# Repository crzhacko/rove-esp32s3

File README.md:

# ROVE — ESP32-S3 RC/Voice Car Platform

Offline voice-controlled toy car platform based on the **ESP32-S3-WROOM-1**.
No internet required — all speech recognition runs on-device via
[ESP-SR](https://github.com/espressif/esp-sr).

## Variants

| Variant  | Motors | Servos | Voice | PCB            |
|----------|:------:|:------:|:-----:|----------------|
| ROVE     | ✓      |        |       | placeholder    |
| ROVE-S   | ✓      | ✓      |       | placeholder    |
| ROVE-V   | ✓      |        | ✓     | **routed** ✓   |
| ROVE-SV  | ✓      | ✓      | ✓     | placeholder    |
| ROVE-SVX | ✓      | ✓      | ✓+    | placeholder    |

See [`docs/rove_variants.md`](docs/rove_variants.md) for full pin assignment,
build instructions, and BOM.

## Repository layout

```
rove_esp32s3/
├── electronics/
│   ├── libs/               shared KiCad symbols (TODO: rove.kicad_sym)
│   ├── rove/               ROVE placeholder schematic
│   ├── rove_s/             ROVE-S placeholder schematic
│   ├── rove_v/             ROVE-V full KiCad schematic + routed PCB ← start here
│   ├── rove_sv/            ROVE-SV placeholder schematic
│   └── rove_svx/           ROVE-SVX placeholder schematic
├── firmware/
│   ├── CMakeLists.txt      top-level ESP-IDF project
│   ├── main/               app_main, Kconfig variant selector
│   ├── components/
│   │   ├── motor/          DRV8833 DC motor driver
│   │   ├── servo/          LEDC PWM servo driver
│   │   └── voice/          INMP441 I2S + ESP-SR recognition pipeline
│   └── configs/            per-variant sdkconfig fragments
├── tools/                  Python scripts for KiCad generation
└── docs/
    ├── rove_variants.md    variant comparison + build guide
    └── bom/                per-variant bill of materials
```

## Quick start (ROVE-V)

```bash
# 1. Install ESP-IDF v5.x
# 2. Clone and enter firmware directory
cd firmware

# 3. Apply ROVE-V sdkconfig
cp configs/sdkconfig.rove_v sdkconfig.defaults

# 4. Build and flash
idf.py set-target esp32s3
idf.py build
idf.py -p /dev/ttyUSB0 flash monitor
```

Wake word: **"Hey ESP"** — then say "go forward", "turn left", "stop", etc.

## Hardware (ROVE-V)

- **MCU**: ESP32-S3-WROOM-1 (16 MB flash, 8 MB PSRAM)
- **Motor driver**: DRV8833PW dual H-bridge
- **Charger**: TP4056 via USB-C (580 mA)
- **LDO**: XC6220B331MR (3.3 V)
- **Microphone**: INMP441 I2S MEMS
- **Board**: 60 × 50 mm (smaller than Arduino Uno)

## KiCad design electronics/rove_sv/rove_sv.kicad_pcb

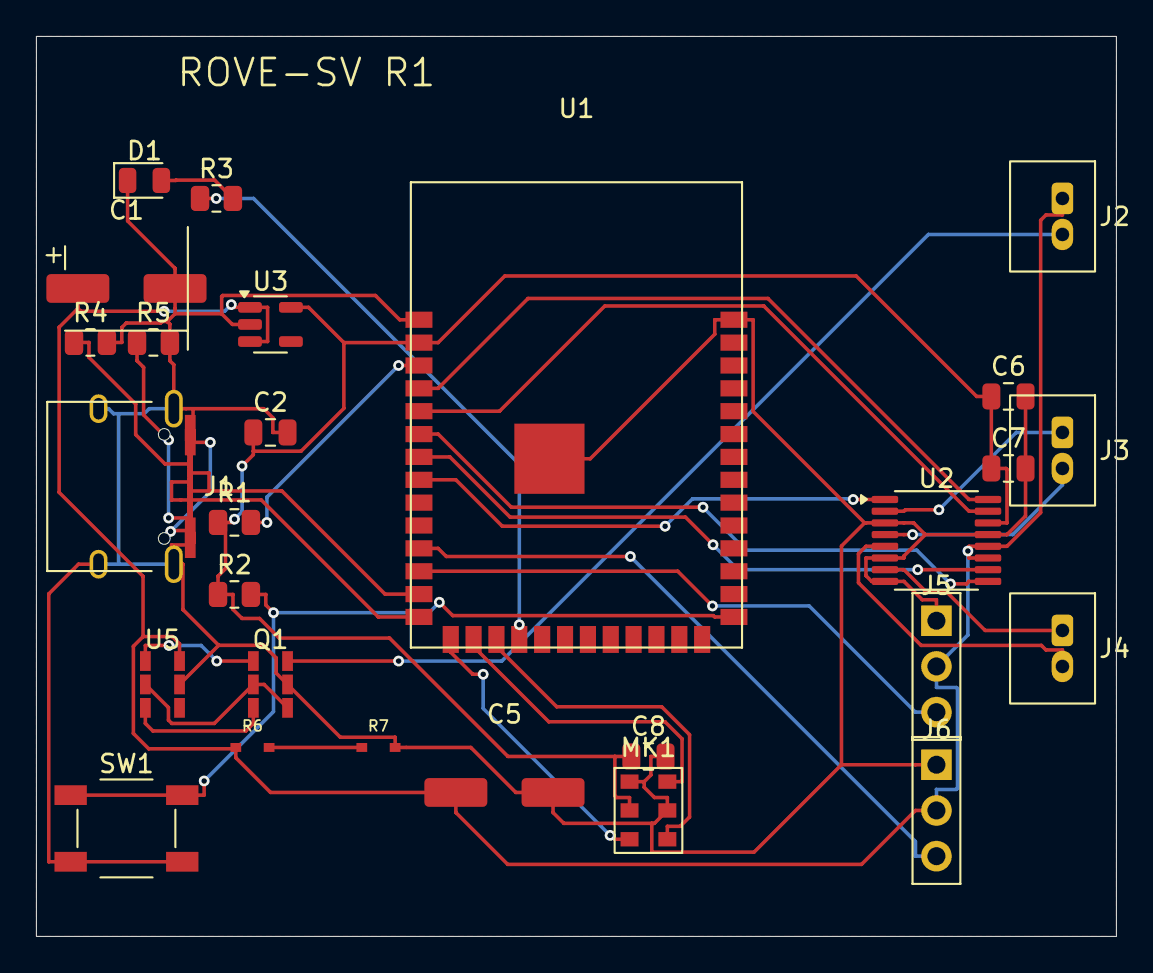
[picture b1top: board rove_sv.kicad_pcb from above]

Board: 2 copper layers, 60.0 x 50.0 mm, 27 parts (0 on the bottom side), 31 nets.

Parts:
C1: 10uF; CP_Elec_6.3x5.8
C2, C7: 0.1uF; C_0805_2012Metric
C5: 100uF; CP_Elec_6.3x5.8
C6: 10nF; C_0805_2012Metric
C8: 100nF; C_0805_2012Metric
D1: Blue; LED_0805_2012Metric
J1: USB-C; USB_C_Receptacle_HRO_TYPE-C-31-M-12
J2: Battery; JST_PH_B2B-PH-K_1x02_P2.00mm_Vertical
J3: LeftMotor; JST_PH_B2B-PH-K_1x02_P2.00mm_Vertical
J4: RightMotor; JST_PH_B2B-PH-K_1x02_P2.00mm_Vertical
J5: Servo1; PinHeader_1x03_P2.54mm_Vertical
J6: Servo2; PinHeader_1x03_P2.54mm_Vertical
MK1: INMP441; INMP441_LGA-6
Q1: FS8205A; SOT-23-6
R1, R2: 10k; R_0805_2012Metric
R3: 330R; R_0805_2012Metric
R4, R5: 5.1k; R_0805_2012Metric
R6: 100k; R_0402_1005Metric
R7: 47k; R_0402_1005Metric
SW1: BOOT; SW_SPST_SKQG_WithoutStem
U1: ESP32-S3-WROOM-1
U2: DRV8833PW; TSSOP-16_4.4x5mm_P0.65mm
U3: XC6220B331MR; SOT-23-5
U5: DW01A; SOT-23-6

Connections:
/3V3: C2.1, C6.1, C7.1, C8.1, MK1.4, R1.1, R2.1, U1.2, U2.14, U3.5
/AOUT1: J3.1, U2.2
/AOUT2: J3.2, U2.4
/BATT_NEG: J2.2, Q1.4
/BOUT1: J4.1, U2.7
/BOUT2: J4.2, U2.5
/CC1: J1.A5, R4.1
/CC2: J1.B5, R5.1
/DRV_SLEEP: U1.8, U2.1
/DW01_OC: Q1.3, U5.3
/DW01_OD: Q1.1, U5.1
/EN: R1.2, U1.3
/I2S_SCK: MK1.6, U1.16
/I2S_SD: MK1.2, U1.17
/I2S_WS: MK1.5, U1.15
/IO0: R2.2, SW1.1, U1.27
/LED_ANODE: D1.A, R3.2
/LEFT_IN1: U1.4, U2.16
/LEFT_IN2: U1.5, U2.15
/PROT_CS: Q1.2, Q1.6, U5.2
/RIGHT_IN1: U1.6, U2.9
/RIGHT_IN2: U1.7, U2.10
/SERVO1: J5.3, U1.12
/SERVO2: J6.3, U1.11
/STATUS_LED: R3.1, U1.18
/USB_5V: J1.A4, J1.A9, J1.B4, J1.B9
/USB_D+: J1.A6, J1.B6, U1.14
/USB_D-: J1.A7, J1.B7, U1.13
/VBAT: C1.1, C5.1, J2.1, J5.2, J6.2, R6.1, U2.11, U2.12, U3.1, U3.3, U5.4
/VBAT_MON: R6.2, R7.1
GND: C1.2, C2.2, C5.2, C6.2, C7.2, C8.2, D1.K, J1.A1, J1.A12, J1.B1, J1.B12, J1.S1, J5.1, J6.1, MK1.1, MK1.3, Q1.5, R4.2, R5.2, R7.2, SW1.2, U1.1, U1.40, U1.41, U2.3, U2.6, U2.8, U2.13, U3.2, U5.5

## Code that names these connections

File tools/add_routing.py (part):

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# ── net numbers (from (net N "name") declarations) ────────────────────────────
GND        = 1
V3V3       = 2
USB_5V     = 3
VBAT       = 4
LEFT_IN1   = 11
LEFT_IN2   = 12
RIGHT_IN1  = 13
RIGHT_IN2  = 14
DRV_SLEEP  = 15
AOUT1      = 16
AOUT2      = 17
BOUT1      = 18
BOUT2      = 19
I2S_WS     = 22
I2S_SCK    = 23
I2S_SD     = 24

# ── absolute pad positions (component_pos + relative_pad_pos) ─────────────────
# U1 ESP32-S3-WROOM-1 @ (30, 25) — left-side pads (x=-8.75 rel)
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
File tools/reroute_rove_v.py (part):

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T(21.25, 28.63, 21.5, 28.63, F_CU, "/DRV_SLEEP", W)
V(21.5, 28.63, "/DRV_SLEEP")
T(21.5, 28.63, 21.5, 50.0, B_CU, "/DRV_SLEEP", W)    # south (clear of I2S/IO0 which go to y≤48.6)
T(21.5, 50.0, 55.0, 50.0, B_CU, "/DRV_SLEEP", W)     # east to x=55
T(55.0, 50.0, 55.0, 31.5, B_CU, "/DRV_SLEEP", W)     # north (x=55 west of all motor south columns)
V(55.0, 31.5, "/DRV_SLEEP")
T(55.0, 31.5, 65.138, 31.5, F_CU, "/DRV_SLEEP", W)   # east at y=31.5 (above 3V3 bus at y=34.05)
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#   VBAT B.Cu col (y=18→42), I2S/IO0 verticals (x=23-39, all west of south columns x≥57)
# Column x: AOUT1=73, AOUT2=74.5, BOUT2=77.5, BOUT1=79 (VBAT B.Cu at x=76 between BOUT2/BOUT1)
# F.Cu approaches: AOUT1 y=21, AOUT2 y=19 (different y to avoid crossing)
# BOUT2 exits west to x=58.5 so its B.Cu south col doesn't cross AOUT1 east at y=44
# =============================================================================
# AOUT1: U2.pad2 (65.138,33.375) → J3.pad1 (70,20)
# Via at x=64 (stub stays x>62.05 so no overlap with 3V3 F.Cu bus).
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# F.Cu approach at y=23 separates from AOUT2 at y=19 (4mm gap).
T(65.138, 33.375, 64.0, 33.375, F_CU, "/AOUT1", W)    # short W stub (x≥62.05 ✓)
V(64.0, 33.375, "/AOUT1", drill=0.4, size=0.8)
T(64.0, 33.375, 64.0, 44.0, B_CU, "/AOUT1", WM)      # south to y=44
T(64.0, 44.0, 73.5, 44.0, B_CU, "/AOUT1", WM)        # east at y=44 to x=73.5
T(73.5, 44.0, 73.5, 23.0, B_CU, "/AOUT1", WM)        # north col x=73.5 (J4.pad2 copper edge=72.6; gap=73.0-72.6=0.4mm ✓)
V(73.5, 23.0, "/AOUT1", drill=0.4, size=0.8)
T(73.5, 23.0, 70.0, 23.0, F_CU, "/AOUT1", WM)        # west at y=23
T(70.0, 23.0, 70.0, 20.0, F_CU, "/AOUT1", WM)        # south → J3.pad1

# AOUT2: U2.pad4 (65.138,34.675) → J3.pad2 (72,20)
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T(58.5, 46.5, 77.5, 46.5, B_CU, "/BOUT2", WM)       # east at y=46.5
T(77.5, 46.5, 77.5, 27.0, B_CU, "/BOUT2", WM)       # north to y=27 (x=77.5 east of VBAT x=76)
V(77.5, 27.0, "/BOUT2", drill=0.4, size=0.8)
T(77.5, 27.0, 72.0, 27.0, F_CU, "/BOUT2", WM)       # west at y=27
T(72.0, 27.0, 72.0, 28.0, F_CU, "/BOUT2", WM)       # → J4.pad2

# BOUT1: U2.pad7 (65.138,36.625) → J4.pad1 (70,28)
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T(31.7, 53.0, 24.9, 53.0, F_CU, "/STATUS_LED", W)       # west to x=24.9
T(24.9, 53.0, 24.9, 43.0, F_CU, "/STATUS_LED", W)       # north at x=24.9 (IO0 via right edge=24.0 → gap 0.8mm ✓;
                                                          #   I2S_SCK via at y=37.5 is above north col range y=43-53 ✓)
T(24.9, 43.0, 21.087, 43.0, F_CU, "/STATUS_LED", W)     # west at y=43
T(21.087, 43.0, 21.087, 42.0, F_CU, "/STATUS_LED", W)   # south stub → R3.pad1 (SMD on F.Cu; no via needed)

# LED_ANODE: R3.pad2 (22.913,42) → D1.padA (18.938,41)  [D1 moved to y=41]
# Route at y=41: jog north from R3.pad2, then west to D1.padA.
# Avoids STATUS_LED via at (21.087,42) — via top edge at y=41.7, track bottom at y=40.9 ✓
T(22.913, 42.0, 22.913, 41.0, F_CU, "/LED_ANODE", W)   # north to y=41
T(22.913, 41.0, 18.938, 41.0, F_CU, "/LED_ANODE", W)   # west → D1.padA

# =============================================================================
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
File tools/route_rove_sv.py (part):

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1. Repositions J5 (50,42)->(50,38) and J6 (50,47)->(50,43) to safe positions
2. Adds SERVO1 (net 30) and SERVO2 (net 31) to net table
3. Fixes J5/J6 pad net assignments
4. Updates ESP32 pad 12 (IO8/GPIO12) -> SERVO1, pad 11 (IO18/GPIO11) -> SERVO2
   NOTE: pad 17 (GPIO17) = I2S_SD (used by microphone, NOT touched)
5. Exports DSN, runs freerouting, imports session
"""

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        '3': (NET_SERVO2, '/SERVO2'),
    })

    # 5. Update ESP32 pad 12 (GPIO12, left side, free in ROVE-V) -> SERVO1
    content = fix_esp32_pad_net(content, '12', NET_SERVO1, '/SERVO1')

    # 6. Update ESP32 pad 11 (GPIO11, left side, free in ROVE-V) -> SERVO2
    #    NOTE: pad 17 = GPIO17 = /I2S_SD (microphone) - do NOT touch it
    content = fix_esp32_pad_net(content, '11', NET_SERVO2, '/SERVO2')

    save(PCB_OUT, content)
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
